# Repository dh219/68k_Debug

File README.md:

# 68k_Debug
Expose the pins of a DIP64 MC68000 to pinheaders to aid logic analysis
### Description
68k_Debug is a simple two-layer board that sits between a DIP64 68000 socket and the CPU, exposing via standard 2.54mm pin headers all the pins for easy sniffing by a logic analyser.
### KiCAD 5
The files are presented as a project and library for KiCAD 5. 

Gerbers are also included for ease of production.
### Copyright
Copyright 2022 D Henderson. Released under the terms of the GPLv2.

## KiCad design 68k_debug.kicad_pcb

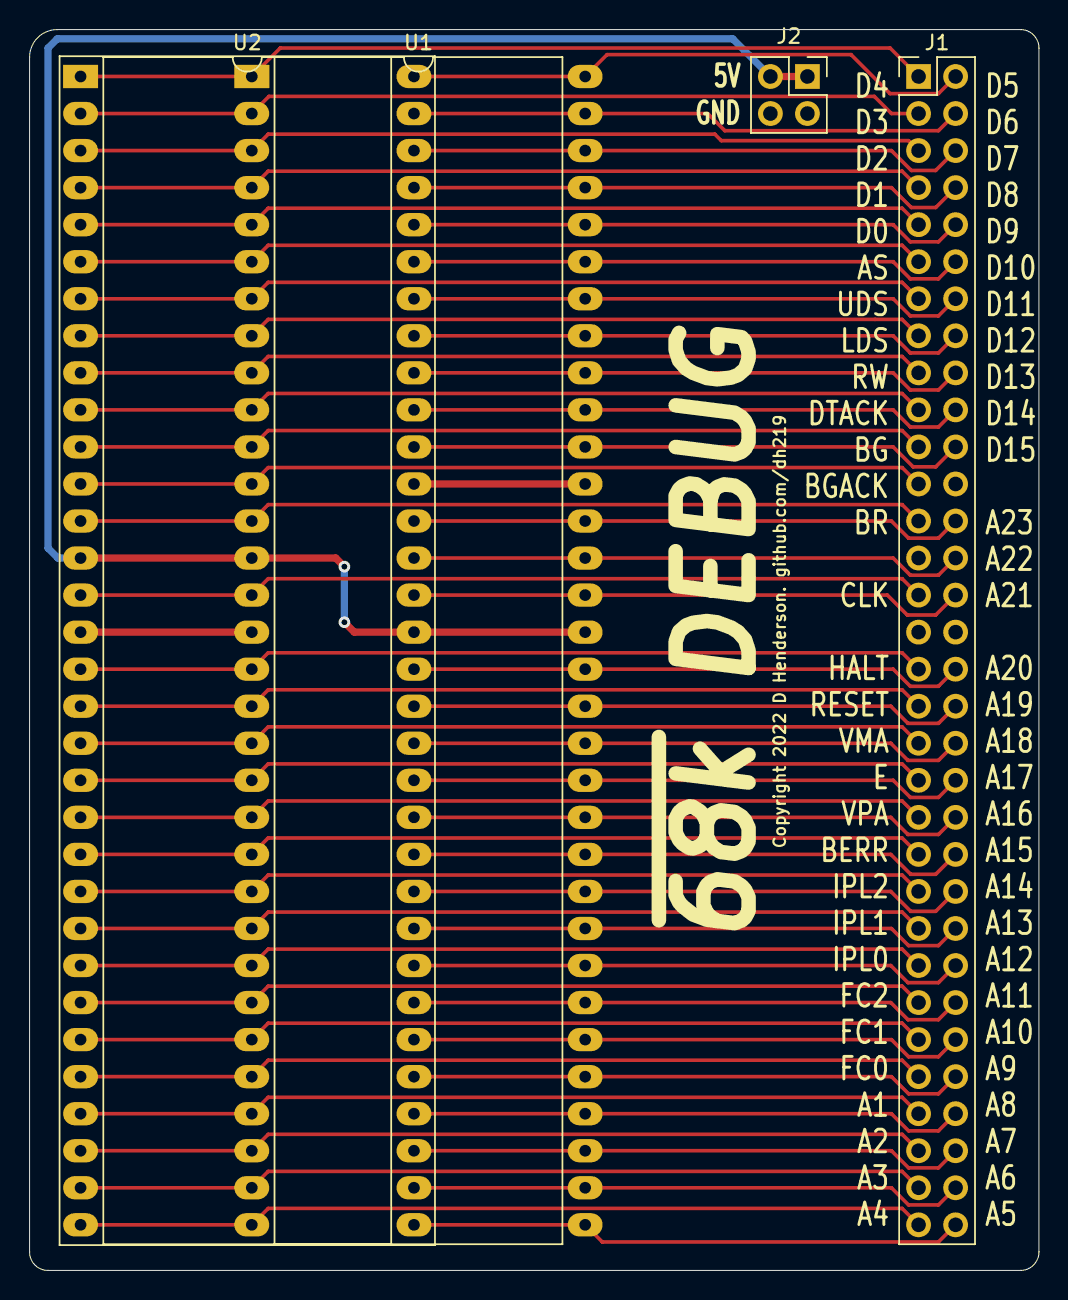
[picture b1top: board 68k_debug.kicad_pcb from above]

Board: 2 copper layers, 69.2 x 85.1 mm, 4 parts (0 on the bottom side), 62 nets.

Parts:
J1: Conn_02x32_Odd_Even; PinHeader_2x32_P2.54mm_Vertical
J2: Conn_02x02_Odd_Even; PinSocket_2x02_P2.54mm_Vertical
U1: 68000D_PLUG; DIP-64_W22.86mm_LongPads
U2: 68000D; DIP-64_W22.86mm_Socket_LongPads

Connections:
+5V: J2.1, J2.2, U1.14, U1.49, U2.14, U2.49
/A1: J1.57, U1.29, U2.29
/A2: J1.59, U1.30, U2.30
/A3: J1.61, U1.31, U2.31
/A4: J1.63, U1.32, U2.32
/A5: J1.64, U1.33, U2.33
/A6: J1.62, U1.34, U2.34
/A7: J1.60, U1.35, U2.35
/A8: J1.58, U1.36, U2.36
/A9: J1.56, U1.37, U2.37
/A10: J1.54, U1.38, U2.38
/A11: J1.52, U1.39, U2.39
/A12: J1.50, U1.40, U2.40
/A13: J1.48, U1.41, U2.41
/A14: J1.46, U1.42, U2.42
/A15: J1.44, U1.43, U2.43
/A16: J1.42, U1.44, U2.44
/A17: J1.40, U1.45, U2.45
/A18: J1.38, U1.46, U2.46
/A19: J1.36, U1.47, U2.47
/A20: J1.34, U1.48, U2.48
/A21: J1.30, U1.50, U2.50
/A22: J1.28, U1.51, U2.51
/A23: J1.26, U1.52, U2.52
/AS: J1.11, U1.6, U2.6
/BERR: J1.43, U1.22, U2.22
/BG: J1.21, U1.11, U2.11
/BGACK: J1.23, U1.12, U2.12
/BR: J1.25, U1.13, U2.13
/CLK: J1.29, U1.15, U2.15
/D0: J1.9, U1.5, U2.5
/D1: J1.7, U1.4, U2.4
/D2: J1.5, U1.3, U2.3
/D3: J1.3, U1.2, U2.2
/D4: J1.1, U1.1, U2.1
/D5: J1.2, U1.64, U2.64
/D6: J1.4, U1.63, U2.63
/D7: J1.6, U1.62, U2.62
/D8: J1.8, U1.61, U2.61
/D9: J1.10, U1.60, U2.60
/D10: J1.12, U1.59, U2.59
/D11: J1.14, U1.58, U2.58
/D12: J1.16, U1.57, U2.57
/D13: J1.18, U1.56, U2.56
/D14: J1.20, U1.55, U2.55
/D15: J1.22, U1.54, U2.54
/DTACK: J1.19, U1.10, U2.10
/E: J1.39, U1.20, U2.20
/FC0: J1.55, U1.28, U2.28
/FC1: J1.53, U1.27, U2.27
/FC2: J1.51, U1.26, U2.26
/HALT: J1.33, U1.17, U2.17
/IPL0: J1.49, U1.25, U2.25
/IPL1: J1.47, U1.24, U2.24
/IPL2: J1.45, U1.23, U2.23
/LDS: J1.15, U1.8, U2.8
/RESET: J1.35, U1.18, U2.18
/RW: J1.17, U1.9, U2.9
/UDS: J1.13, U1.7, U2.7
/VMA: J1.37, U1.19, U2.19
/VPA: J1.41, U1.21, U2.21
GND: J2.3, J2.4, U1.16, U1.53, U2.16, U2.53

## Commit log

2022-07-11 Adding the 68k_Debug board as demonstrated in my PiStorm ST video.
2022-07-11 Adding gerbers

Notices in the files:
68k_debug.kicad_pcb:
Copyright 2022 D Henderson. github.com/dh219
